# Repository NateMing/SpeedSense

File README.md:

# Radar Speed Sign - Custom PCBs

Custom PCB designs for SpeedSense, developed using KiCAD.

## Project Overview

This repository contains the custom PCB designs created for SpeedSense. The PCBs include a main control board and a custom 7-segment display module designed specifically for this application.

## Project Structure

```
├── SDP25_MainPCB_V2/          # Latest main PCB design (v2.1)
├── SDP25_MainPCB/             # Original main PCB design
├── Drill Files/               # Manufacturing files
│   ├── Main PCB 2.1/         # Latest drill files
│   ├── Main PCB/             # Original drill files
│   └── 7 seg/                # 7-segment display drill files
└── segment.kicad_pcb          # 7-segment display PCB
```

## Hardware Components

### Main Control PCB (v2.1)
- **File**: `SDP25_MainPCB_V2.kicad_pcb`
- **Purpose**: Main control board for radar speed sign system
- **Features**: 4-layer PCB design with power and ground planes
- **Layers**: Front/Back copper, Power, Ground
- **Design Rules**: 0.2mm minimum clearance, 0.25mm minimum track width

### Custom 7-Segment Display PCB
- **File**: `segment.kicad_pcb`
- **Purpose**: Large format 7-segment display module for vehicle speed display

## Getting Started

### Prerequisites
- KiCAD 7.0 or later

## Manufacturing Files

Ready-to-manufacture Gerber files are available in:
- `SDP25_MainPCB_V2/Gerbers/` - Latest main PCB
- `Drill Files/Main PCB 2.1/` - Corresponding drill files
- `Drill Files/7 seg/` - 7-segment display files

### File Types Included
- **Gerber files** (.gtl, .gbl, .gts, .gbs, etc.)
- **Drill files** (.drl)
- **Pick and place** (.gbr)
- **Job files** (.gbrjob)

## Design Specifications

- **Board thickness**: Standard 1.6mm
- **Minimum track width**: 0.25mm
- **Minimum via size**: 0.5mm diameter
- **Minimum hole size**: 0.3mm
- **Layer count**: 4 layers (Main PCB v2.1)

## Version History

- **v2.1** (Latest) - 4-layer design with improved power distribution
- **v1.0** - Initial 2-layer design

## Project Context

These PCBs are part of a larger radar speed sign system developed as a Senior Design Project (SDP). The complete system includes:
- Radar sensor integration
- Microcontroller-based speed processing
- Custom display driver circuitry
- Power management systems

This repository contains only the custom PCB designs created specifically for this project.

## License

This project is for educational purposes as part of academic coursework.

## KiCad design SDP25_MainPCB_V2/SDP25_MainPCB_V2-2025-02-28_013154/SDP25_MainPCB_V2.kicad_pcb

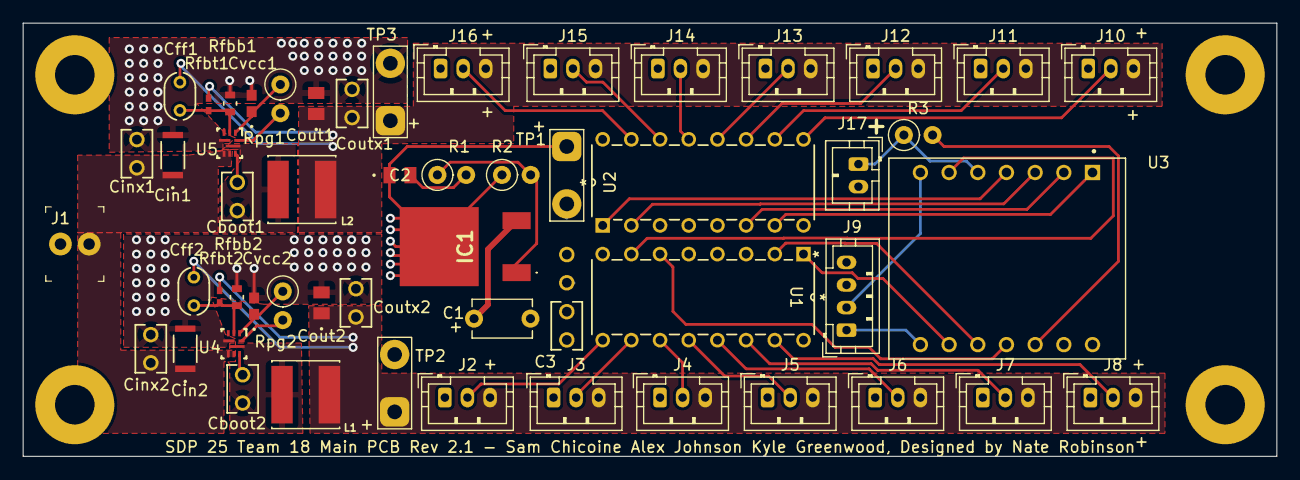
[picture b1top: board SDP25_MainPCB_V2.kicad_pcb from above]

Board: 4 copper layers, 111.0 x 38.4 mm, 55 parts (1 on the bottom side), 42 nets.

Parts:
C1: 10uF; C_Disc_D5.1mm_W3.2mm_P5.00mm
C2: 22uF; CAP_GRM21B_MUR
C3, C4: 0.1uF; CAP_FG18_TDK
Cboot1, Cboot2: 0.1uF; CAP_FG18_TDK
Cff1, Cff2: 15pF; CAP_FA18_TDK
Cin1, Cin2: 33uF; CAP_3216_TDK
Cinx1, Cinx2: 0.1uF; CAP_FG18_TDK
Cout1, Cout2: 22uF; CAP_GRM21B_MUR
Coutx1, Coutx2: 0.1uF; CAP_FG18_TDK
Cvcc1, Cvcc2: 1uF; cap_UMK107ABJ474KA-T_TAY
IC1: 5V Voltage Reg.; AZ1084CDADJTRG1
J1: Battery Conn; PinHeader_1x2_P2.54mm_Drill1.02mm
J2: D1PCB1; JST_PH_B3B-PH-K_1x03_P2.00mm_Vertical
J3: D1PCB2; JST_PH_B3B-PH-K_1x03_P2.00mm_Vertical
J4: D1PCB3; JST_PH_B3B-PH-K_1x03_P2.00mm_Vertical
J5: D1PCB4; JST_PH_B3B-PH-K_1x03_P2.00mm_Vertical
J6: D1PCB5; JST_PH_B3B-PH-K_1x03_P2.00mm_Vertical
J7: D1PCB6; JST_PH_B3B-PH-K_1x03_P2.00mm_Vertical
J8: D1PCB7; JST_PH_B3B-PH-K_1x03_P2.00mm_Vertical
J9: Radar Conn; JST_PH_B4B-PH-K_1x04_P2.00mm_Vertical
J10: D2PCB1; JST_PH_B3B-PH-K_1x03_P2.00mm_Vertical
J11: D2PCB2; JST_PH_B3B-PH-K_1x03_P2.00mm_Vertical
J12: D2PCB3; JST_PH_B3B-PH-K_1x03_P2.00mm_Vertical
J13: D2PCB4; JST_PH_B3B-PH-K_1x03_P2.00mm_Vertical
J14: D2PCB5; JST_PH_B3B-PH-K_1x03_P2.00mm_Vertical
J15: D2PCB6; JST_PH_B3B-PH-K_1x03_P2.00mm_Vertical
J16: D2PCB7; JST_PH_B3B-PH-K_1x03_P2.00mm_Vertical
J17: Setup Connector; JST_PH_B2B-PH-K_1x02_P2.00mm_Vertical
L1, L2: 1uH; IND_VLS6045EX-1R0N
R1: 150; R_Axial_DIN0207_L6.3mm_D2.5mm_P2.54mm_Vertical
R2: 56; R_Axial_DIN0207_L6.3mm_D2.5mm_P2.54mm_Vertical
R3: R; R_Axial_DIN0207_L6.3mm_D2.5mm_P2.54mm_Vertical
Rfbb1, Rfbb2: 30k; RES_RC0603_YAG
Rfbt1, Rfbt2: 95.3k; RC0402N_VIS
Rpg1, Rpg2: 100k; R_Axial_DIN0207_L6.3mm_D2.5mm_P2.54mm_Vertical
TP1: TP 5V; TestPoint_2Pads_Pitch5.08mm_Drill1.3mm
TP2, TP3: TP 2.5V; TestPoint_2Pads_Pitch5.08mm_Drill1.3mm
U1: BCD-To-7 2; N16
U2: BCD-TO-7 1; N16
U3: XIAO ESP32C3; MODULE_113991054
U4, U5: TPS566238PRQFR; RQF0009A

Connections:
/SW1: Cboot1.1, L2.1, U5.8 (SW)
/SW2: Cboot2.1, L1.1, U4.8 (SW)
/Vin: C1.1, Cin1.1, Cin2.1, Cinx1.1, Cinx2.1, IC1.3 (INPUT), J1.1, J9.3, U4.5 (VIN), U4.6 (VIN), U5.5 (VIN), U5.6 (VIN)
/Vout1: Cff2.1, Cout2.1, Coutx2.1, J2.3, J3.3, J4.3, J5.3, J6.3, J7.3, J8.3, L1.2, Rfbt2.1, TP2.1
/Vout2: Cff1.1, Cout1.1, Coutx1.1, J10.3, J11.3, J12.3, J13.3, J14.3, J15.3, J16.3, L2.2, Rfbt1.1, TP3.1
/Vout3: C2.1, C3.2, C4.1, IC1.2 (OUTPUT), R2.1, TP1.1, U1.3 (*LT), U1.4 (*BL), U1.16 (VCC), U2.3 (*LT), U2.4 (*BL), U2.16 (VCC), U3.14 (VUSB)
GND: C1.2, C2.2, C3.1, C4.2, Cin1.2, Cin2.2, Cinx1.2, Cinx2.2, Cout1.2, Cout2.2, Coutx1.2, Coutx2.2, Cvcc1.2, Cvcc2.2, J1.2, J2.1, J3.1, J4.1, J5.1, J6.1, J7.1, J8.1, J9.4, J10.1, J11.1, J12.1, J13.1, J14.1, J15.1, J16.1, J17.2, R1.2, Rfbb1.2, Rfbb2.2, TP1.2, TP2.2, TP3.2, U1.5 (*LE), U1.8 (GND), U2.5 (*LE), U2.8 (GND), U3.13 (GND), U4.4 (PGND), U5.4 (PGND)
unnamed: IC1.1 (ADJ), R1.1, R2.2
unnamed: J6.2, U1.13 (A)
unnamed: J5.2, U1.12 (B)
unnamed: J4.2, U1.11 (C)
unnamed: U1.7 (D0), U3.6 (D5)
unnamed: U1.1 (D1), U3.9 (D8)
unnamed: U1.2 (D2), U3.10 (D9)
unnamed: U1.6 (D3), U3.11 (D10)
unnamed: J3.2, U1.10 (D)
unnamed: J2.2, U1.9 (E)
unnamed: J8.2, U1.15 (F)
unnamed: J7.2, U1.14 (G)
unnamed: J14.2, U2.13 (A)
unnamed: J13.2, U2.12 (B)
unnamed: J12.2, U2.11 (C)
unnamed: U2.7 (D0), U3.1 (D0)
unnamed: U2.1 (D1), U3.4 (D3)
unnamed: U2.2 (D2), U3.3 (D2)
unnamed: U2.6 (D3), U3.2 (D1)
unnamed: J11.2, U2.10 (D)
unnamed: J10.2, U2.9 (E)
unnamed: J16.2, U2.15 (F)
unnamed: J15.2, U2.14 (G)
unnamed: J17.1, R3.1, U3.5 (D4)
unnamed: J9.1, U3.8 (RX_D7)
unnamed: J9.2, U3.7 (TX_D6)
unnamed: R3.2, U3.12 (VCC_3V3)
unnamed: Cboot2.2, U4.7 (BST)
unnamed: Cff2.2, Rfbb2.1, Rfbt2.2, U4.2 (FB)
unnamed: Rpg2.2, U4.9 (SS)
unnamed: Cvcc2.1, Rpg2.1, U4.1 (VCC)
unnamed: Cboot1.2, U5.7 (BST)
unnamed: Cff1.2, Rfbb1.1, Rfbt1.2, U5.2 (FB)
unnamed: Rpg1.2, U5.9 (SS)
unnamed: Cvcc1.1, Rpg1.1, U5.1 (VCC)

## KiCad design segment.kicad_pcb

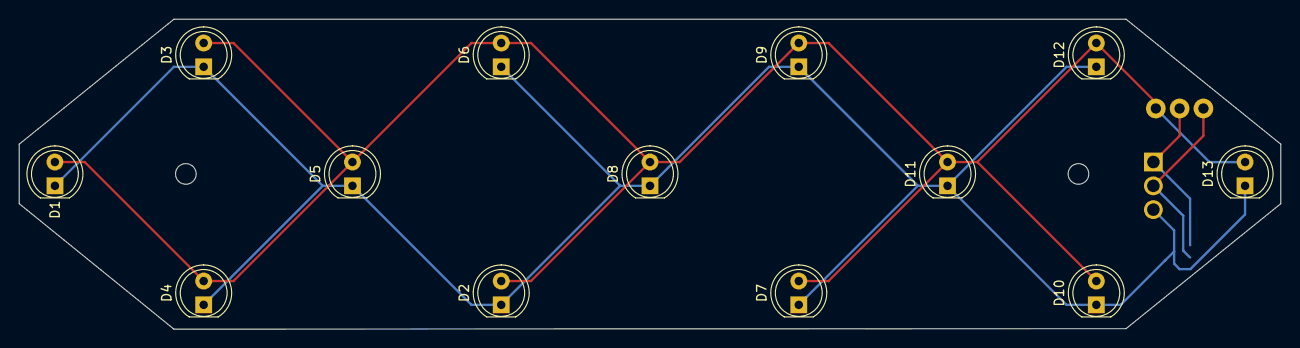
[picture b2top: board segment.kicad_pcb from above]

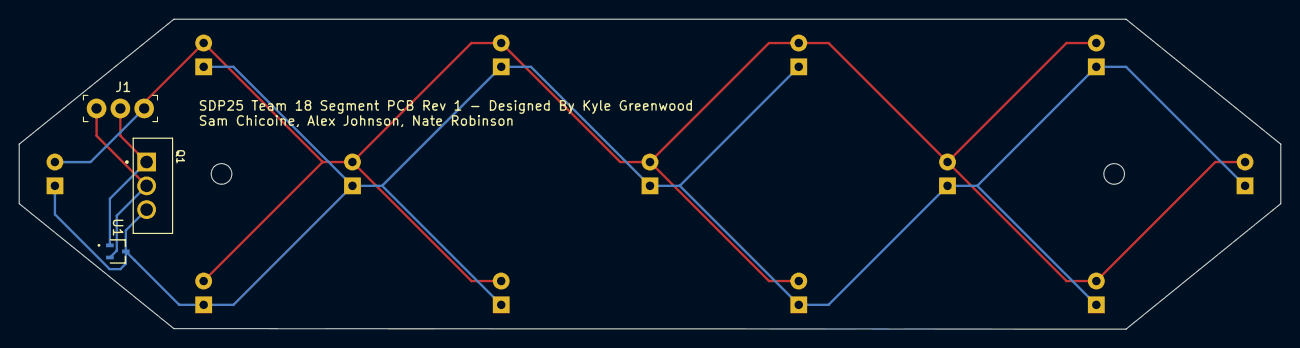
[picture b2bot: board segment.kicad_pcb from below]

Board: 2 copper layers, 134.6 x 33.1 mm, 16 parts (3 on the bottom side), 4 nets.

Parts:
D1, D2, D3, D4, D5, D6, D7, D8, D9, D10, D11, D12, D13: LED; LED_D5.0mm
J1: 61300311121; PinHeader_1x3_P2.54_Drill1.1mm
Q1: DN2540N5-G; TO254P1066X482X2286-3
U1: DMG1012UW-7; SOT_12UW-7_DIO-L

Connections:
unnamed: D1.2 (A), D2.2 (A), D3.2 (A), D4.2 (A), D5.2 (A), D6.2 (A), D7.2 (A), D8.2 (A), D9.2 (A), D10.2 (A), D11.2 (A), D12.2 (A), D13.2 (A), J1.3
unnamed: D1.1 (K), D2.1 (K), D3.1 (K), D4.1 (K), D5.1 (K), D6.1 (K), D7.1 (K), D8.1 (K), D9.1 (K), D10.1 (K), D11.1 (K), D12.1 (K), D13.1 (K), Q1.3, U1.3 (S)
unnamed: J1.1, Q1.2, U1.2 (D)
unnamed: J1.2, Q1.1, U1.1 (G)

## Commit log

2025-09-02 Init
2025-10-23 Added pictyures and videos of operation
